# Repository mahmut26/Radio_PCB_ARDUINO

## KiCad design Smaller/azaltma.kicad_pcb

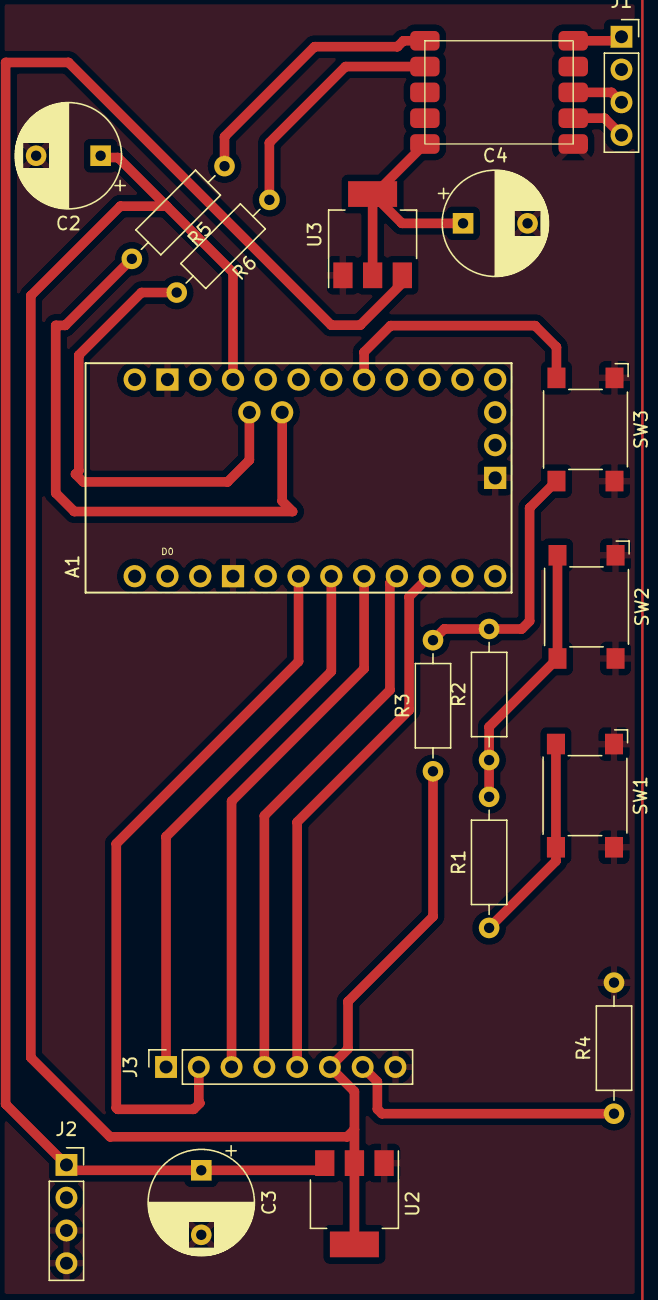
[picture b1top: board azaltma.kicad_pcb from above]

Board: 2 copper layers, 19 parts (0 on the bottom side), 20 nets.

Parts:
A1: Clone_Pro_Mini_Socket_NoSPH
C2, C3, C4: C; CP_Radial_D8.0mm_P5.00mm
J1, J2: Conn_01x04_Socket; PinSocket_1x04_P2.54mm_Vertical
J3: Conn_01x08_Pin; PinSocket_1x08_P2.54mm_Vertical
R1, R2, R3, R4, R5, R6: R; R_Axial_DIN0207_L6.3mm_D2.5mm_P10.16mm_Horizontal
SW1, SW2, SW3: SW_Push; SW_SPST_Omron_B3FS-100xP
U1: rda
U2: AMS1117-5.0; SOT-223-3_TabPin2
U3: AMS1117-3.3; SOT-223-3_TabPin2

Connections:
+3.3V: C4.1, U1.5 (3.3V), U3.2 (VO)
+5V: A1.Vcc1 (Vcc), C2.1, J3.6, R3.1, U2.2 (VO)
GND: A1.GND1 (GND), A1.GND2 (GND), A1.GND3 (GND), C2.2, C3.2, C4.2, J2.3, J2.4, J3.8, R4.2, SW1.1, SW2.1, SW3.1, U1.10 (GND), U2.1 (GND), U3.1 (GND)
unnamed: A1.A4 (A4/SDA), R5.2
unnamed: A1.A5 (A5/SCL), R6.2
unnamed: A1.D3 (D3_INT1), J3.2
unnamed: A1.A0, R2.2, R3.2, SW3.2
unnamed: J1.1, U1.6 (ANT)
unnamed: J1.3, U1.8 (HOP)
unnamed: J1.4, U1.9 (HOP)
unnamed: C3.1, J2.1, J2.2, U2.3 (VI), U3.3 (VI)
unnamed: A1.D4, J3.1
unnamed: A1.D5, J3.3
unnamed: A1.D6, J3.4
unnamed: A1.D7, J3.5
unnamed: J3.7, R4.1
unnamed: R1.1, SW1.2
unnamed: R1.2, R2.1, SW2.2
unnamed: R5.1, U1.1 (SCA)
unnamed: R6.1, U1.2 (SCL)
